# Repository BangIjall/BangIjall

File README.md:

- Hi, I’m Muhammad Rayhan Rizaldi 👋
- I’m interested in robotic
- If u like my projects and want to collaborate with me, u can visit my contacts
- Whatsapp : 082124256955
- Instagram : @rizaldirayhn
- Twitter : @BangIjalll
- Email : mr.rizaldi1629@gmail.com

<!---
BangIjall/BangIjall is a ✨ special ✨ repository because its `README.md` (this file) appears on your GitHub profile.
You can click the Preview link to take a look at your changes.
--->

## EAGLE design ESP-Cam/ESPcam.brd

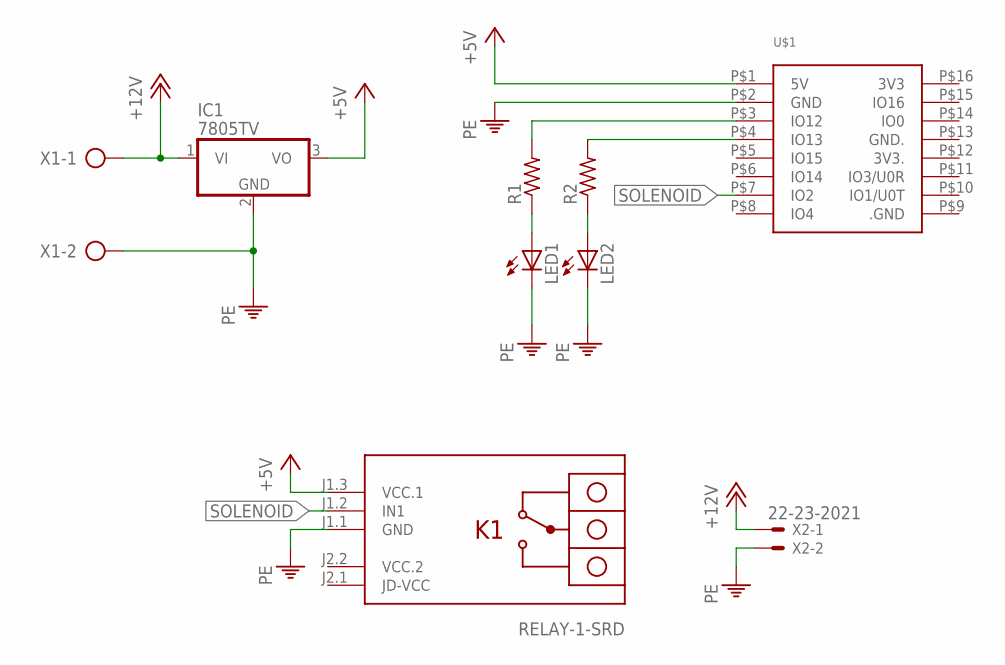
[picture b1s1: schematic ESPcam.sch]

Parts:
IC1: 7805TV; TO220V
LED1, LED2: LED5MM
R1, R2: R-US_0207/15; 0207/15
U$1: ESP32-CAM
U$2: RELAY-1-SRD
X1: AK500/2-H
X2: 22-23-2021

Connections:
+5V: IC1.3 (VO), U$1.P$1 (5V), U$2.J1.3 (VCC.1)
+12V: IC1.1 (VI), X1.1, X2.1
unnamed: LED1.A, R1.1
unnamed: LED2.A, R2.1
unnamed: R1.2, U$1.P$3 (IO12)
unnamed: R2.2, U$1.P$4 (IO13)
PE: IC1.2 (GND), LED1.K (C), LED2.K (C), U$1.P$2 (GND), U$2.J1.1 (GND), X1.2, X2.2
SOLENOID: U$1.P$7 (IO2), U$2.J1.2 (IN1)
VCC.2: U$2.J2.2 (VCC.2)

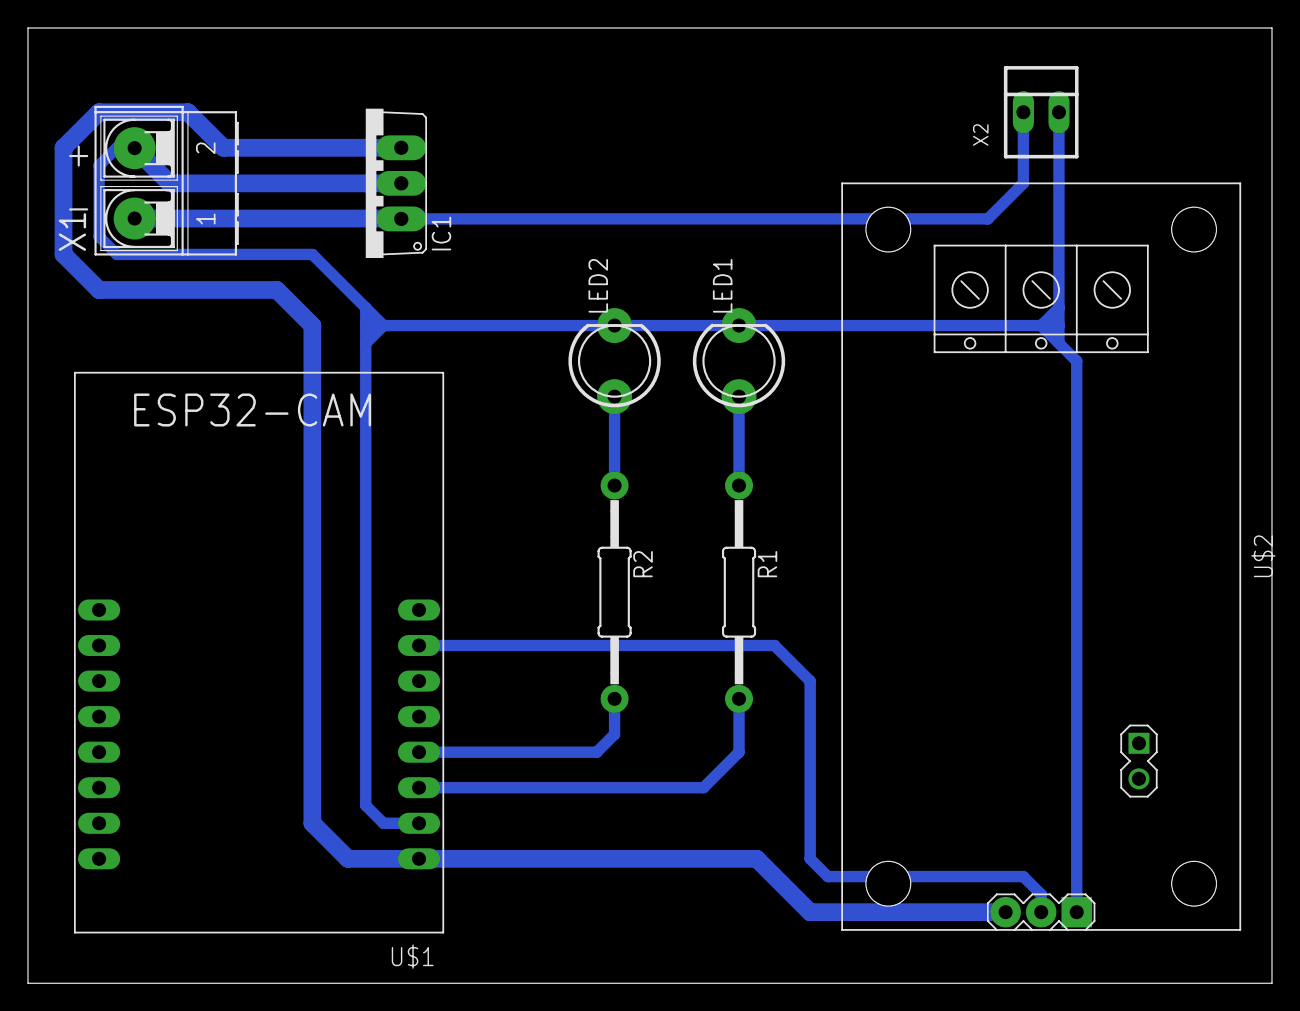
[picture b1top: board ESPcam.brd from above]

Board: 2 copper layers, 88.9 x 68.2 mm, 9 parts (0 on the bottom side), 8 nets.

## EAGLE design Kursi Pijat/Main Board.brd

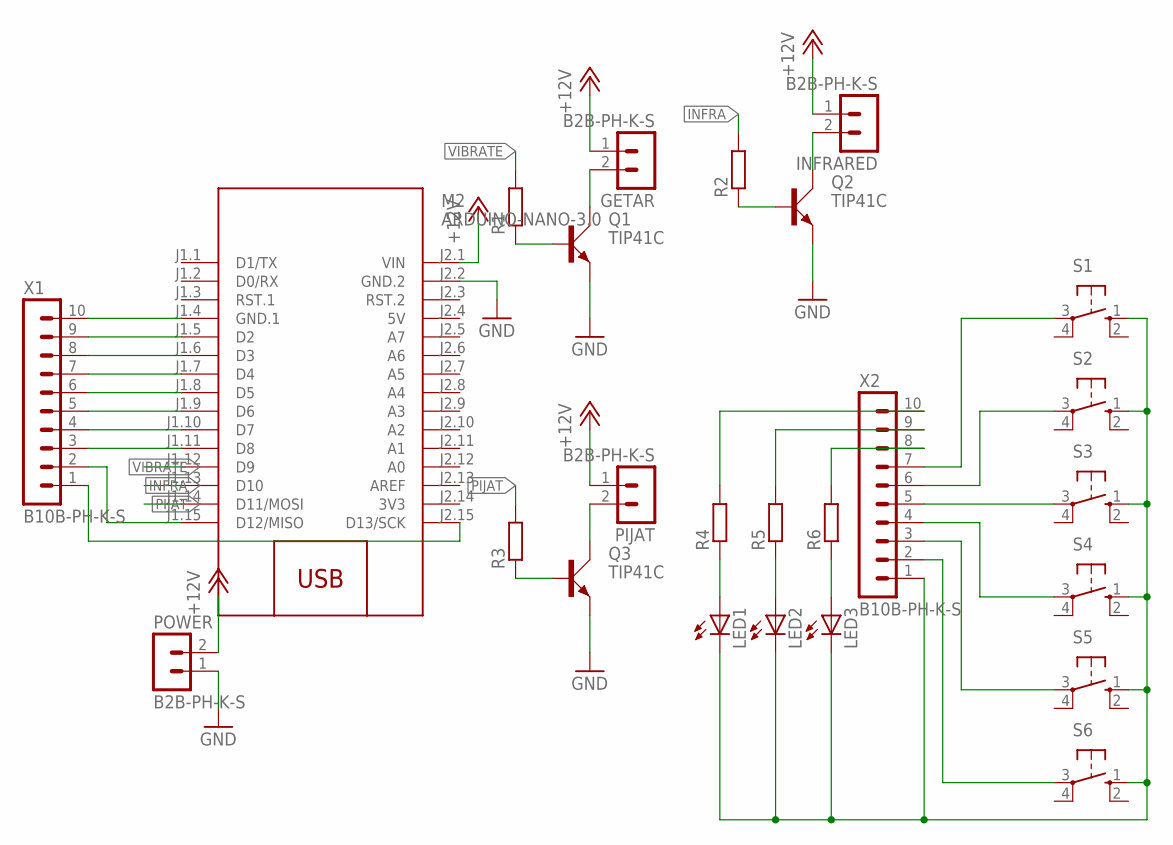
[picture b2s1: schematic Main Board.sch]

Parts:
GETAR: B2B-PH-K-S
INFRARED: B2B-PH-K-S
LED1, LED2, LED3: LED5MM
M2: ARDUINO-NANO-3.0
PIJAT: B2B-PH-K-S
POWER: B2B-PH-K-S
Q1, Q2, Q3: TIP41C; TO220AV
R1, R2, R3, R4, R5, R6: R-EU_0207/12; 0207/12
S1, S2, S3, S4, S5, S6: 40-XX; B3F-40XX
X1, X2: B10B-PH-K-S

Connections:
3V3: M2.J2.14 (3V3)
5V: M2.J2.4 (5V)
+12V: GETAR.1, INFRARED.1, M2.J2.1 (VIN), PIJAT.1, POWER.2
GND: M2.J2.2 (GND.2), POWER.1, Q1.E, Q2.E, Q3.E
INFRA: M2.J1.13 (D10), R2.2
unnamed: INFRARED.2, Q2.C
unnamed: GETAR.2, Q1.C
unnamed: PIJAT.2, Q3.C
unnamed: M2.J1.4 (GND.1), X1.10
unnamed: M2.J1.5 (D2), X1.9
unnamed: M2.J1.6 (D3), X1.8
unnamed: M2.J1.7 (D4), X1.7
unnamed: M2.J1.8 (D5), X1.6
unnamed: M2.J1.9 (D6), X1.5
unnamed: Q2.B, R2.1
unnamed: S1.3, X2.7
unnamed: S2.3, X2.6
unnamed: S5.3, X2.3
unnamed: S4.3, X2.4
unnamed: S3.3, X2.5
unnamed: M2.J1.10 (D7), X1.4
unnamed: Q1.B, R1.1
unnamed: Q3.B, R3.1
unnamed: M2.J1.11 (D8), X1.3
unnamed: M2.J1.15 (D12/MISO), X1.2
unnamed: S6.3, X2.2
unnamed: M2.J2.15 (D13/SCK), X1.1
unnamed: LED1.A, R4.1
unnamed: LED2.A, R5.1
unnamed: LED3.A, R6.1
unnamed: R4.2, X2.10
unnamed: R5.2, X2.9
unnamed: R6.2, X2.8
unnamed: LED1.K (C), LED2.K (C), LED3.K (C), S1.1 (S), S2.1 (S), S3.1 (S), S4.1 (S), S5.1 (S), S6.1 (S), X2.1
PIJAT: M2.J1.14 (D11/MOSI), R3.2
VIBRATE: M2.J1.12 (D9), R1.2

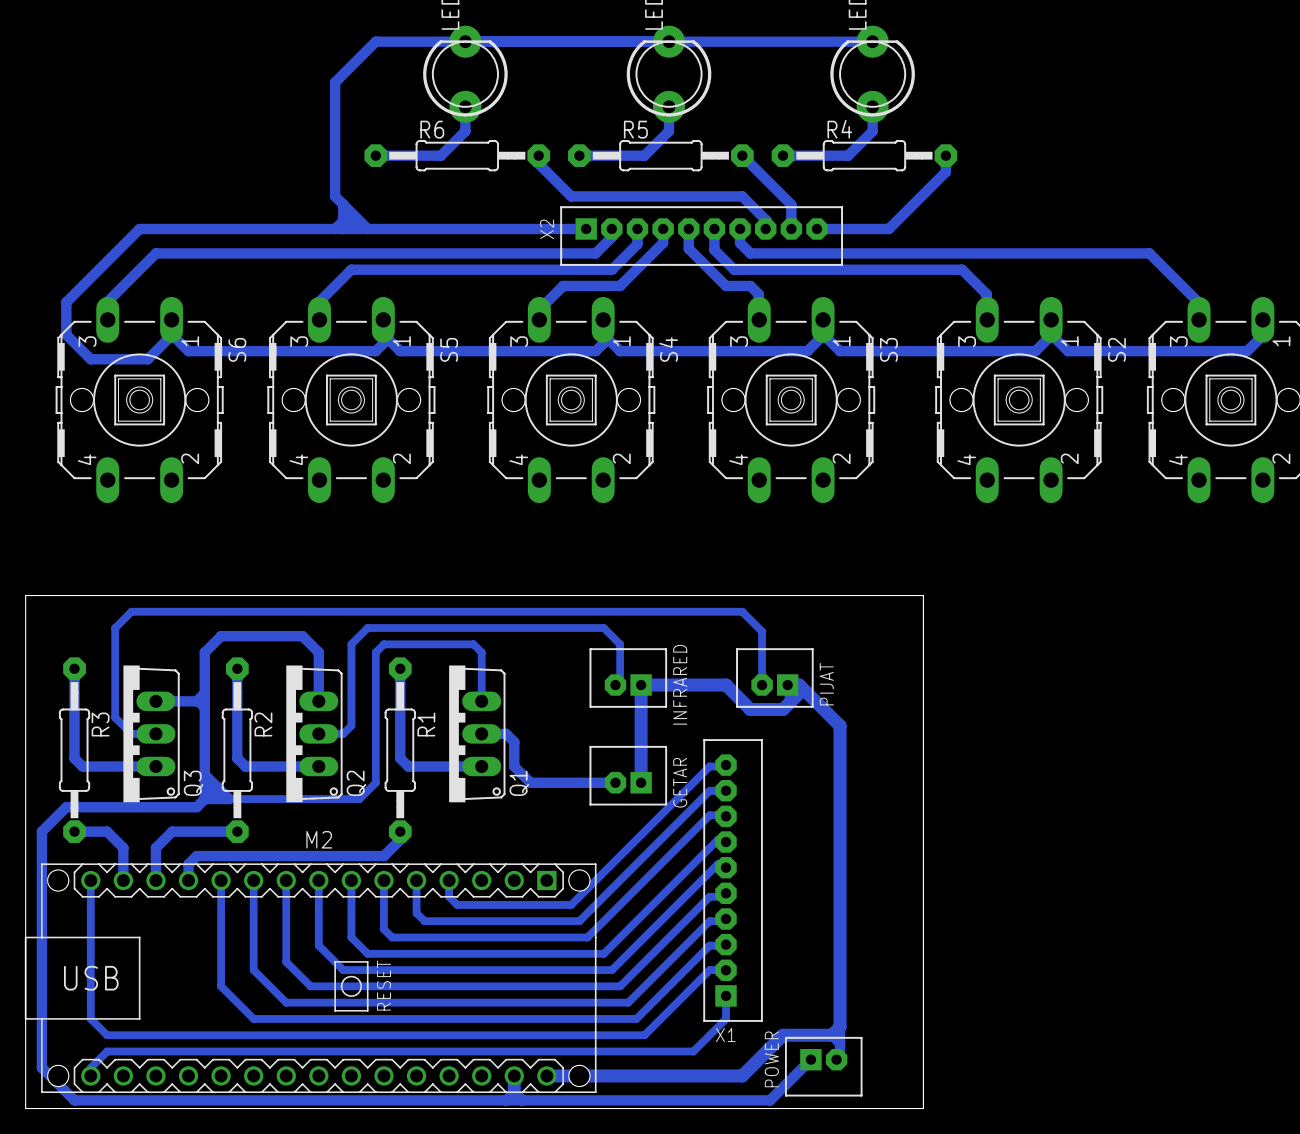
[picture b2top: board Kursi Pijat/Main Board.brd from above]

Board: 2 copper layers, 70.0 x 40.0 mm, 25 parts (0 on the bottom side), 34 nets.

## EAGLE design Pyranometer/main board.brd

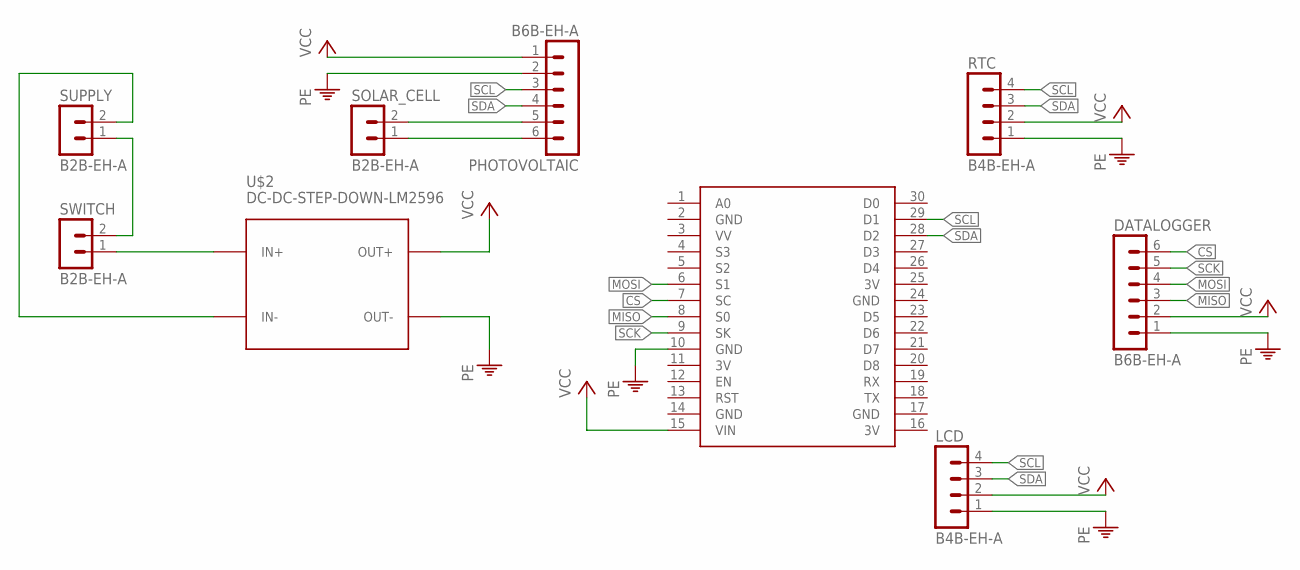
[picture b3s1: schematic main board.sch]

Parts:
DATALOGGER: B6B-EH-A
LCD: B4B-EH-A
PHOTOVOLTAIC: B6B-EH-A
RTC: B4B-EH-A
SOLAR_CELL: B2B-EH-A
SUPPLY: B2B-EH-A
SWITCH: B2B-EH-A
U$1: NODEMCU
U$2: DC-DC-STEP-DOWN-LM2596

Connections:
3V: U$1.11 (3V), U$1.16 (3V), U$1.25 (3V)
CS: DATALOGGER.6, U$1.7 (SC)
GND: U$1.2 (GND), U$1.14 (GND), U$1.17 (GND), U$1.24 (GND)
MISO: DATALOGGER.3, U$1.8 (S0)
MOSI: DATALOGGER.4, U$1.6 (S1)
unnamed: PHOTOVOLTAIC.6, SOLAR_CELL.1
unnamed: SUPPLY.2, U$2.IN-
unnamed: SUPPLY.1, SWITCH.2
unnamed: SWITCH.1, U$2.IN+
unnamed: PHOTOVOLTAIC.5, SOLAR_CELL.2
PE: DATALOGGER.1, LCD.1, PHOTOVOLTAIC.2, RTC.1, U$1.10 (GND), U$2.OUT-
SCK: DATALOGGER.5, U$1.9 (SK)
SCL: LCD.4, PHOTOVOLTAIC.3, RTC.4, U$1.29 (D1)
SDA: LCD.3, PHOTOVOLTAIC.4, RTC.3, U$1.28 (D2)
VCC: DATALOGGER.2, LCD.2, PHOTOVOLTAIC.1, RTC.2, U$1.15 (VIN), U$2.OUT+

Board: 2 copper layers, 9 parts (0 on the bottom side), 15 nets, no tracks yet.

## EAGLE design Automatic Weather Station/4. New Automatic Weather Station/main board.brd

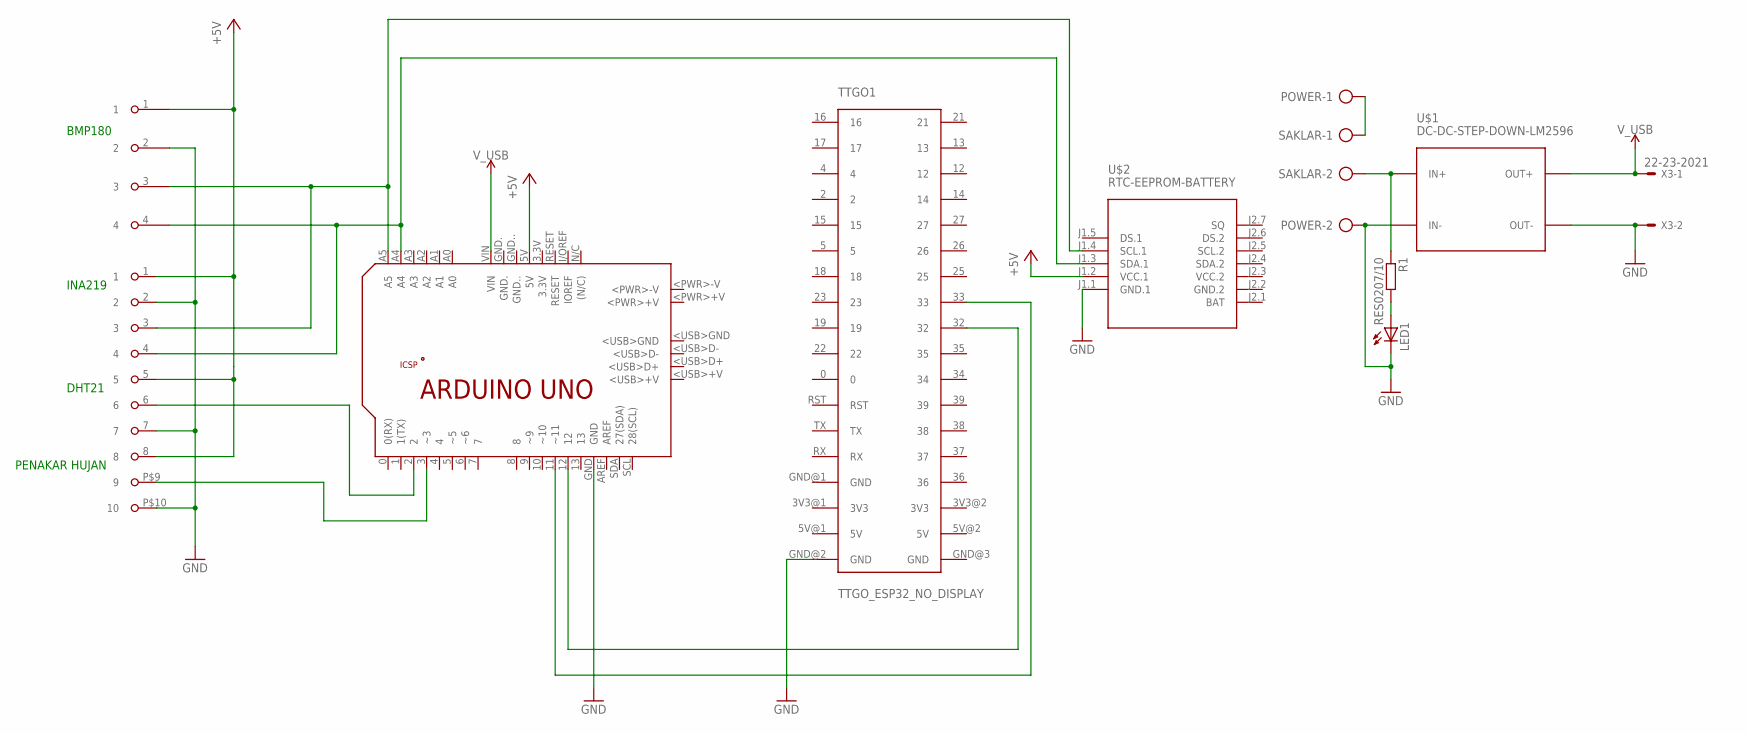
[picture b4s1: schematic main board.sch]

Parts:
LED1: LED5MM
PCB1: ARDUINO_UNO
POWER: AK500/2-H
R1: RES0207/10; 0207/10
SAKLAR: AK500/2-H
TTGO1: TTGO_ESP32_NO_DISPLAY
U$1: DC-DC-STEP-DOWN-LM2596
U$2: RTC-EEPROM-BATTERY
U$3: CON-10TA
U$4: CON-4NEW2; CON-4NEW
X3: 22-23-2021

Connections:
+5V: PCB1.5V, U$2.J1.2 (VCC.1), U$3.1, U$3.5, U$3.8, U$4.1
GND.2: U$2.J2.2 (GND.2)
unnamed: R1.1, SAKLAR.2, U$1.IN+
unnamed: LED1.A, R1.2
unnamed: POWER.1, SAKLAR.1
unnamed: PCB1.A5, U$2.J1.4 (SCL.1), U$3.3, U$4.3
unnamed: PCB1.A4, U$2.J1.3 (SDA.1), U$3.4, U$4.4
unnamed: PCB1.2, U$3.6
unnamed: PCB1.3 (~3), U$3.P$9 (9)
unnamed: PCB1.11 (~11), TTGO1.33
unnamed: PCB1.12, TTGO1.32
unnamed: LED1.K (C), PCB1.GND, POWER.2, TTGO1.GND@2 (GND), U$1.IN-, U$1.OUT-, U$2.J1.1 (GND.1), U$3.2, U$3.7, U$3.P$10 (10), U$4.2, X3.2
VCC.2: U$2.J2.3 (VCC.2)
V_USB: PCB1.VIN, U$1.OUT+, X3.1

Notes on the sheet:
BMP180
INA219
DHT21
PENAKAR HUJAN

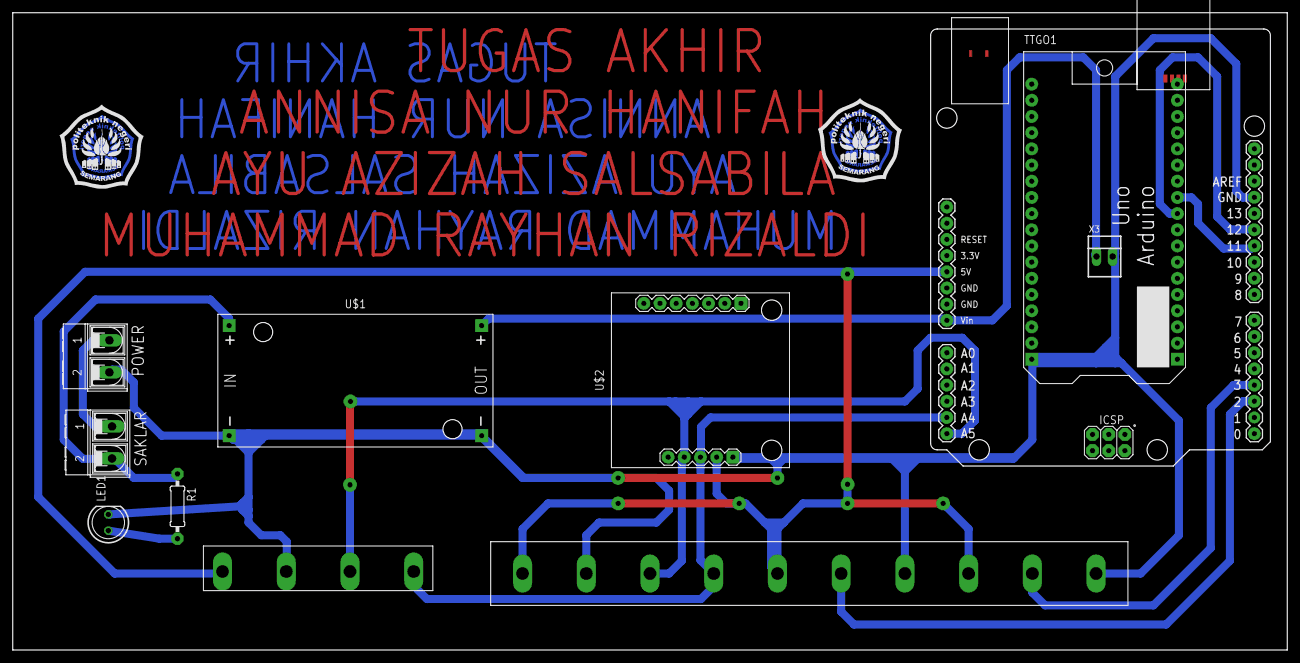
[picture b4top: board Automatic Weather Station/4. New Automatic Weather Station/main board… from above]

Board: 2 copper layers, 200.0 x 100.0 mm, 15 parts (0 on the bottom side), 12 nets.

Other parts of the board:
U$5, U$6: POLINES_10X10_BOT
U$7, U$8: POLINES_13.5X13.5

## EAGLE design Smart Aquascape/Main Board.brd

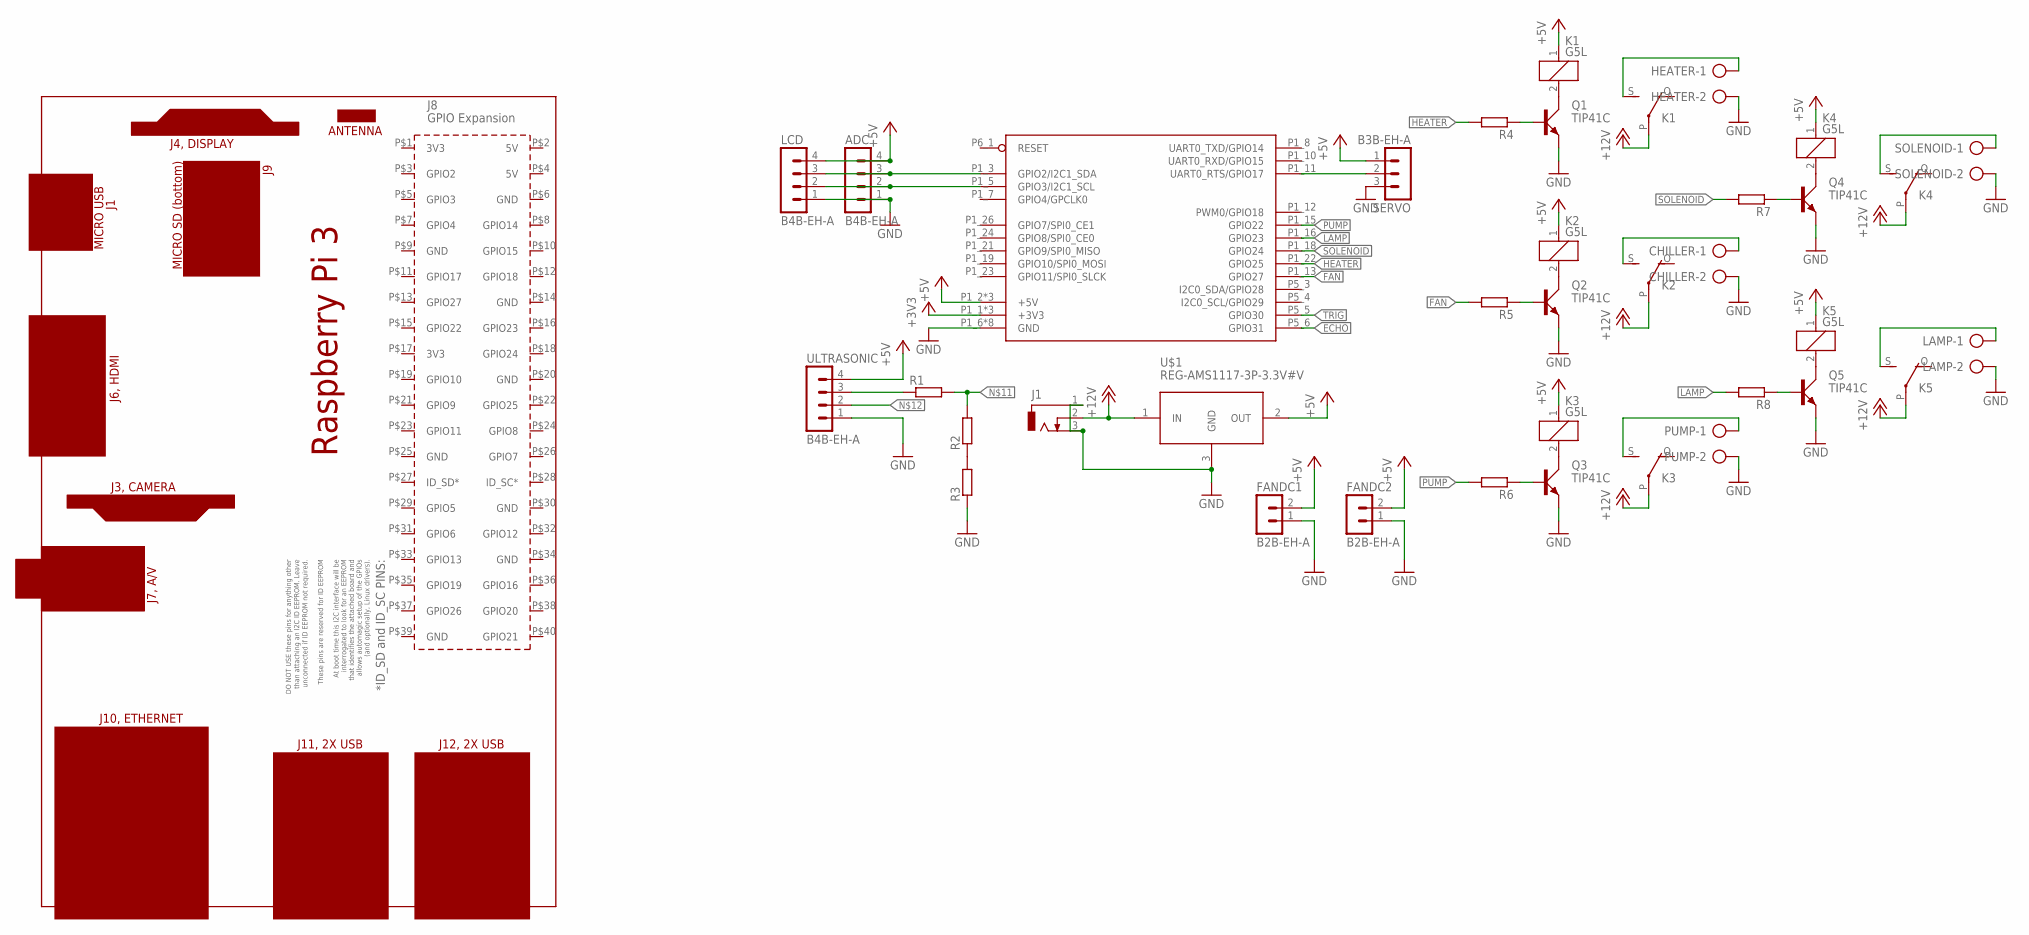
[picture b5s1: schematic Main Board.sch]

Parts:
ADC: B4B-EH-A
CHILLER: AK500/2-H
FANDC1, FANDC2: B2B-EH-A
HEATER: AK500/2-H
J1: DCJ0303
K1, K2, K3, K4, K5: G5L; G5LE
LAMP: AK500/2-H
LCD: B4B-EH-A
PCB1: RPI3
PUMP: AK500/2-H
Q1, Q2, Q3, Q4, Q5: TIP41C; TO220AV
R1, R2, R3, R4, R5, R6, R7, R8: R-EU_0207/15; 0207/15
SERVO: B3B-EH-A
SOLENOID: AK500/2-H
U$1: REG-AMS1117-3P-3.3V#V; REG-AMS1117-3P#V
U$3: RPI-B-V2NO_SHIELD; RPI-B-V2
ULTRASONIC: B4B-EH-A

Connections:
+3V3: U$3.P1_1 (+3V3), U$3.P1_17 (+3V3), U$3.P5_2 (+3V3)
+5V: ADC.4, FANDC1.2, FANDC2.2, K1.1, K2.1, K3.1, K4.1, K5.1, LCD.4, SERVO.1, U$1.2 (OUT), U$3.P1_2 (+5V), U$3.P1_4 (+5V), U$3.P5_1 (+5V), ULTRASONIC.4
+12V: J1.2, K1.P, K2.P, K3.P, K4.P, K5.P, U$1.1 (IN)
ECHO: U$3.P5_6 (GPIO31)
FAN: R5.2, U$3.P1_13 (GPIO27)
GND: ADC.1, CHILLER.2, FANDC1.1, FANDC2.1, HEATER.2, J1.1, J1.3, LAMP.2, LCD.1, PUMP.2, Q1.E, Q2.E, Q3.E, Q4.E, Q5.E, R3.1, SERVO.3, SOLENOID.2, U$1.3 (GND), U$3.P1_6 (GND), U$3.P1_9 (GND), U$3.P1_14 (GND), U$3.P1_20 (GND), U$3.P1_25 (GND), U$3.P5_7 (GND), U$3.P5_8 (GND), U$3.P6_2 (GND), ULTRASONIC.1
HEATER: R4.2, U$3.P1_22 (GPIO25)
I2C0_SCL/GPIO29: U$3.P5_4 (I2C0_SCL/GPIO29)
I2C0_SDA/GPIO28: U$3.P5_3 (I2C0_SDA/GPIO28)
LAMP: R8.2, U$3.P1_16 (GPIO23)
unnamed: ADC.3, LCD.3, U$3.P1_3 (GPIO2/I2C1_SDA)
unnamed: ADC.2, LCD.2, U$3.P1_5 (GPIO3/I2C1_SCL)
unnamed: K3.S, PUMP.1
unnamed: K3.2, Q3.C
unnamed: Q3.B, R6.1
unnamed: CHILLER.1, K2.S
unnamed: HEATER.1, K1.S
unnamed: SERVO.2, U$3.P1_11 (UART0_RTS/GPIO17)
unnamed: R2.1, R3.2
unnamed: R1.1, ULTRASONIC.3
unnamed: R1.2, R2.2
unnamed: K1.2, Q1.C
unnamed: Q1.B, R4.1
unnamed: K2.2, Q2.C
unnamed: Q2.B, R5.1
unnamed: K4.S, SOLENOID.1
unnamed: K4.2, Q4.C
unnamed: Q4.B, R7.1
unnamed: K5.S, LAMP.1
unnamed: K5.2, Q5.C
unnamed: Q5.B, R8.1
PUMP: R6.2, U$3.P1_15 (GPIO22)
RESET: U$3.P6_1 (RESET)
SOLENOID: R7.2, U$3.P1_18 (GPIO24)
TRIG: U$3.P5_5 (GPIO30)

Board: 2 copper layers, 33 parts (0 on the bottom side), 30 nets, no tracks yet.

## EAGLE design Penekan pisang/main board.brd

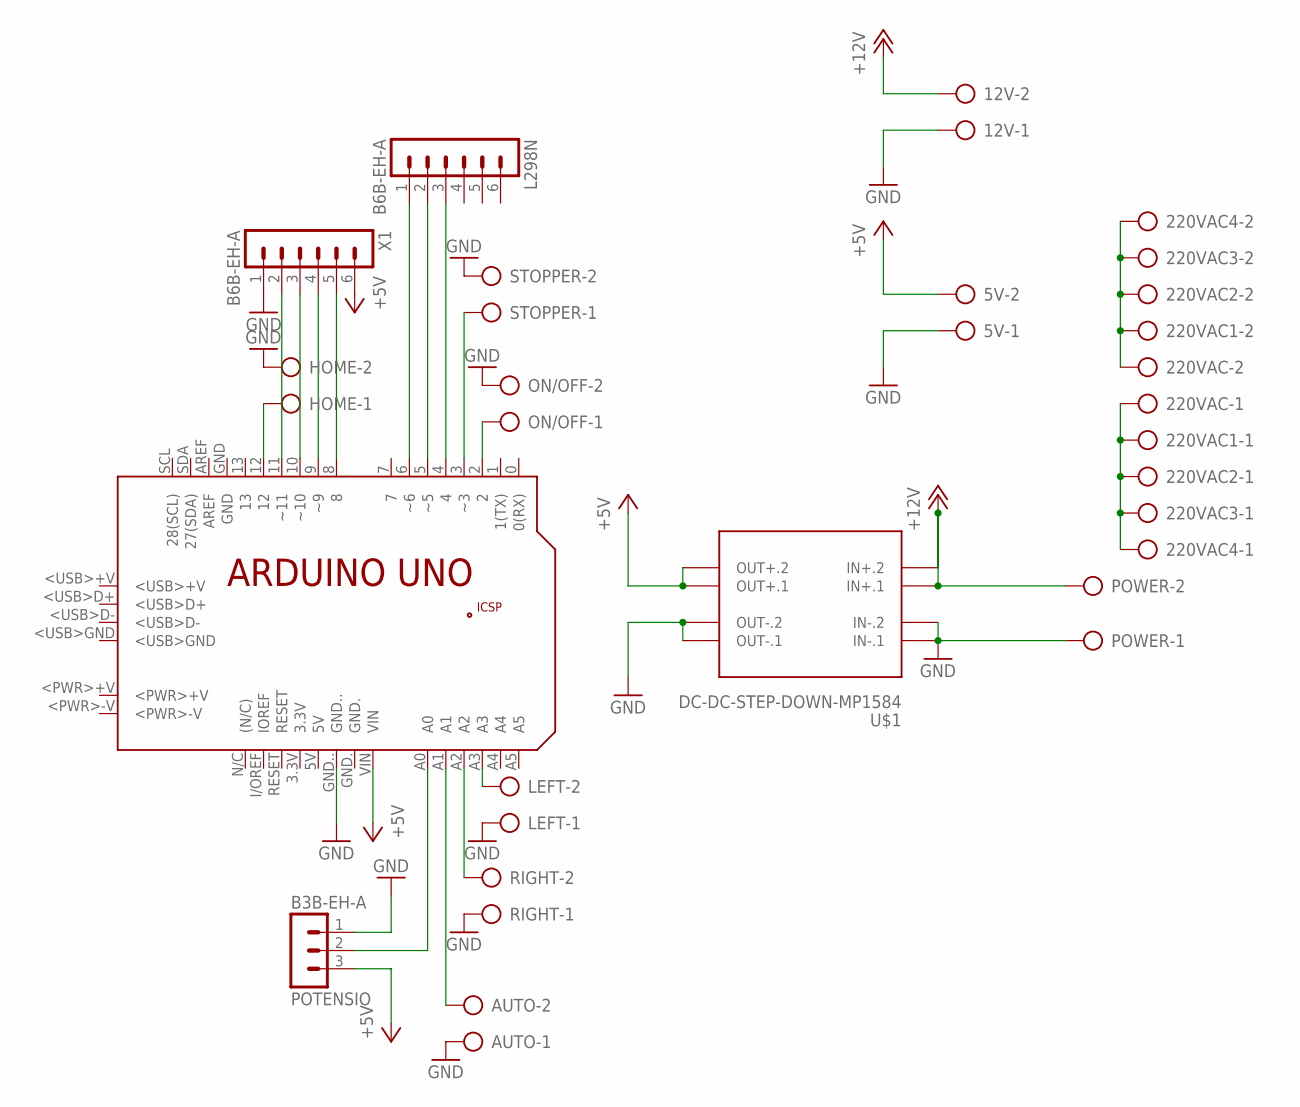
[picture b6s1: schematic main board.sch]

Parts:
5V, 12V, 220VAC, 220VAC1, 220VAC2, 220VAC3, 220VAC4: AK500/2-H
AUTO: AK500/2-H
HOME: AK500/2-H
L298N: B6B-EH-A
LEFT: AK500/2-H
ON/OFF: AK500/2-H
PCB1: ARDUINO_UNO
POTENSIO: B3B-EH-A
POWER: AK500/2-H
RIGHT: AK500/2-H
STOPPER: AK500/2-H
U$1: DC-DC-STEP-DOWN-MP1584
X1: B6B-EH-A

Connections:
+5V: 5V.2, PCB1.VIN, POTENSIO.3, U$1.OUT+.1, U$1.OUT+.2, X1.6
+12V: 12V.2, POWER.2, U$1.IN+.1, U$1.IN+.2
GND: 5V.1, 12V.1, AUTO.1, HOME.2, LEFT.1, ON/OFF.2, PCB1.GND.., POTENSIO.1, POWER.1, RIGHT.1, STOPPER.2, U$1.IN-.1, U$1.IN-.2, U$1.OUT-.1, U$1.OUT-.2, X1.1
unnamed: L298N.2, PCB1.5 (~5)
unnamed: L298N.3, PCB1.4
unnamed: L298N.1, PCB1.6 (~6)
unnamed: AUTO.2, PCB1.A1
unnamed: PCB1.11 (~11), X1.2
unnamed: PCB1.A0, POTENSIO.2
unnamed: PCB1.10 (~10), X1.3
unnamed: PCB1.9 (~9), X1.4
unnamed: PCB1.8, X1.5
unnamed: PCB1.A2, RIGHT.2
unnamed: LEFT.2, PCB1.A3
unnamed: PCB1.3 (~3), STOPPER.1
unnamed: HOME.1, PCB1.12
unnamed: ON/OFF.1, PCB1.2
unnamed: 220VAC.1, 220VAC1.1, 220VAC2.1, 220VAC3.1, 220VAC4.1
unnamed: 220VAC.2, 220VAC1.2, 220VAC2.2, 220VAC3.2, 220VAC4.2

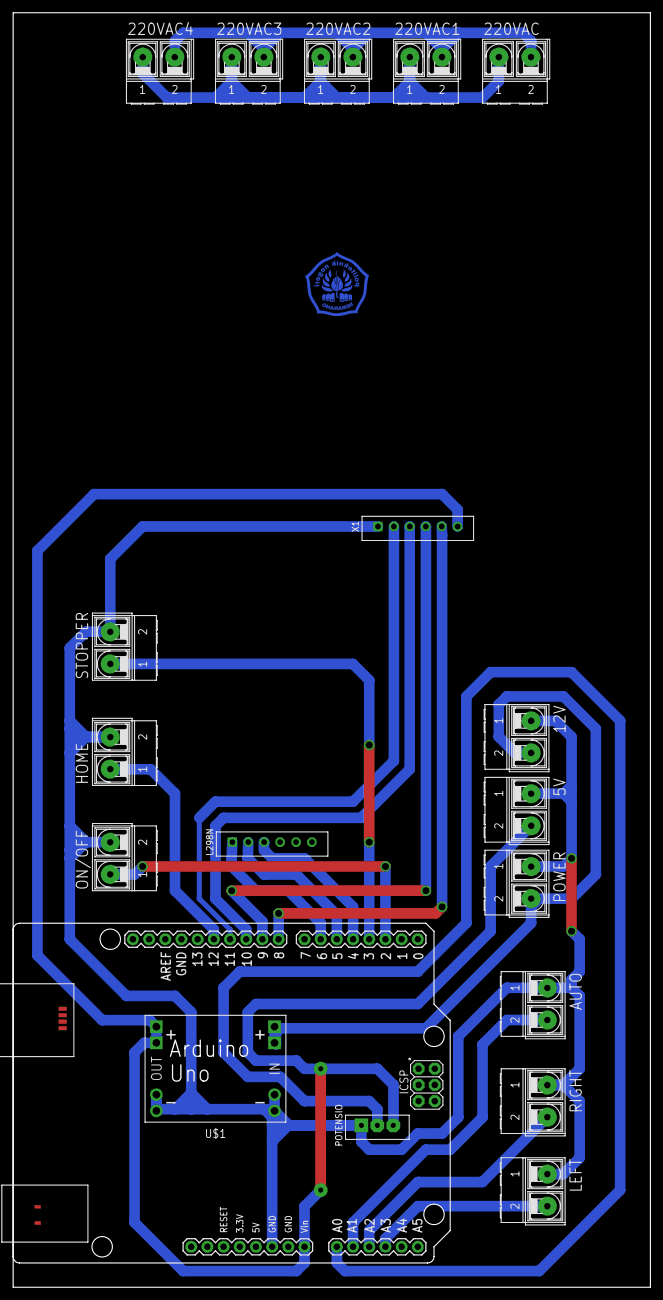
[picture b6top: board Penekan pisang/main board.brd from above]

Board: 2 copper layers, 100.0 x 200.0 mm, 20 parts (0 on the bottom side), 19 nets.

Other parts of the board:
U$2: POLINES_10X10_BOT

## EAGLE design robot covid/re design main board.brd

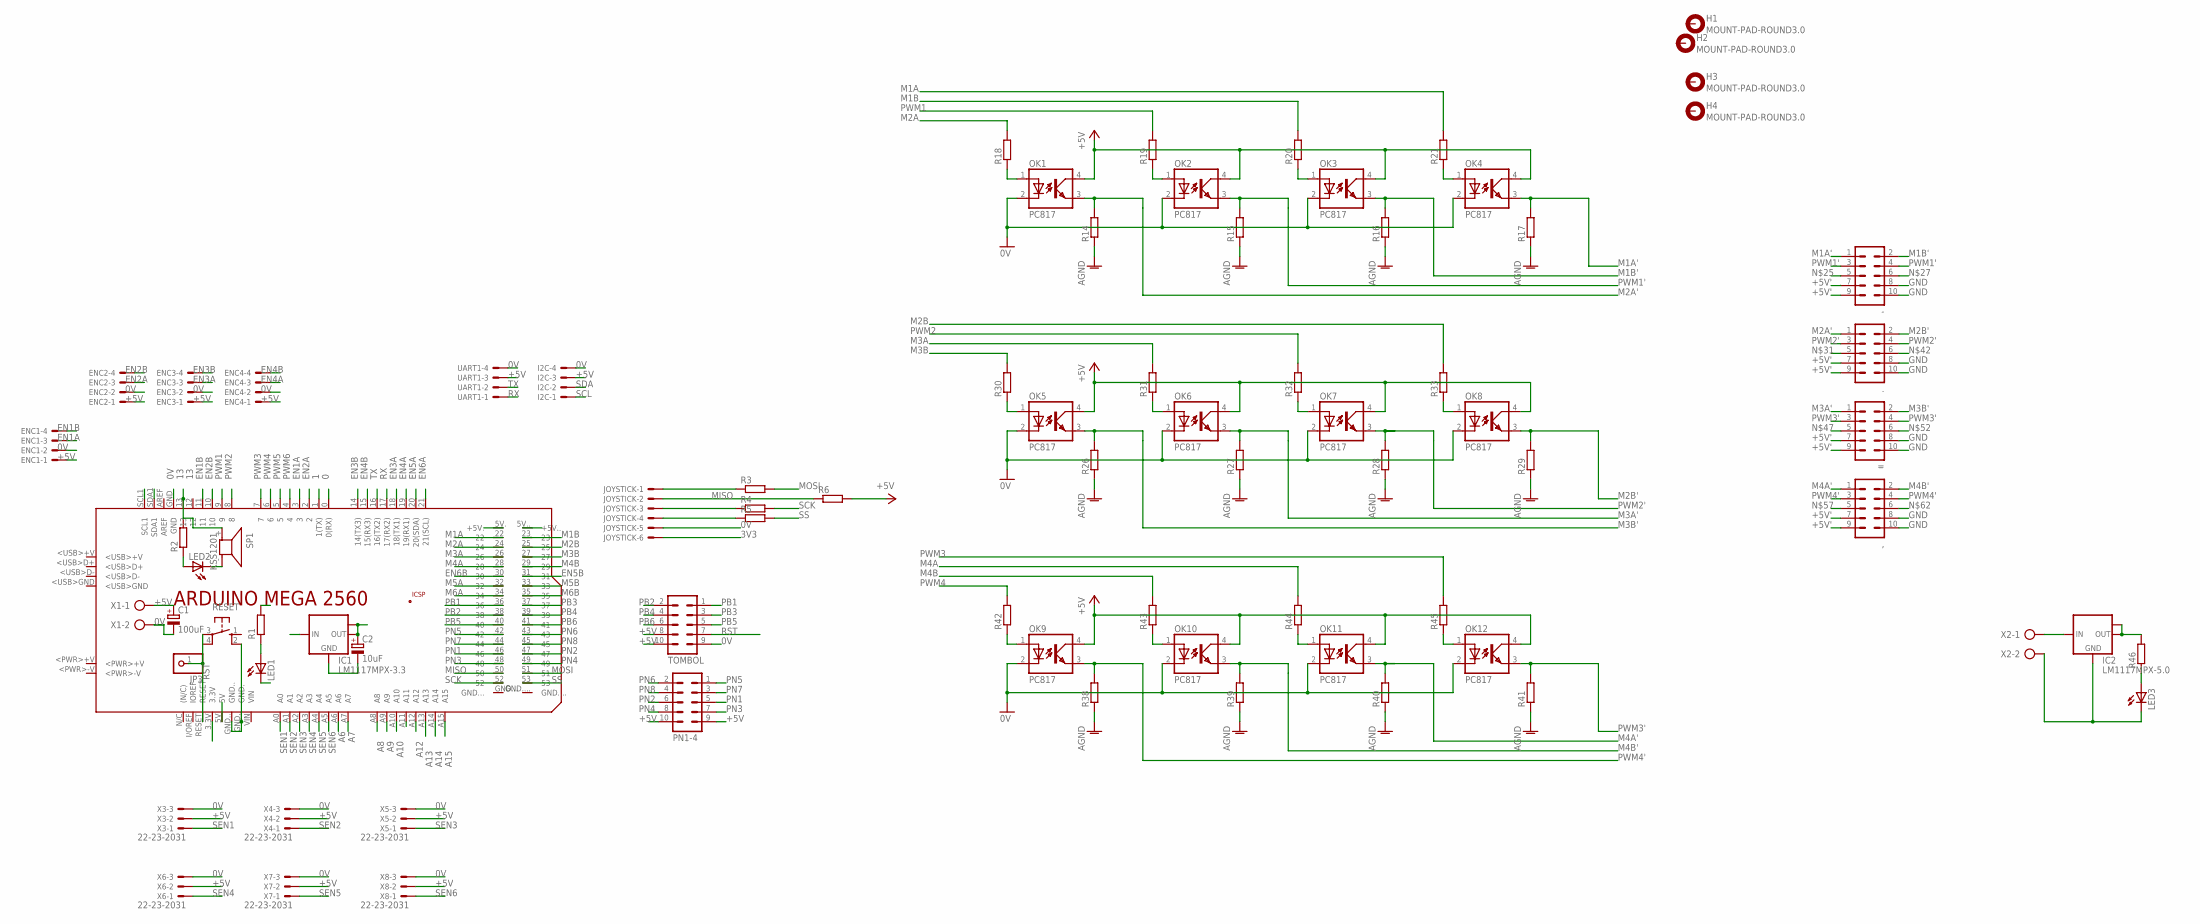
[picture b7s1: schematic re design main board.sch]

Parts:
,: ML10
-: ML10
.: ML10
=: ML10
C1: 100uF; E2,5-5
C2: 10uF; E2,5-5
ENC1, ENC2, ENC3, ENC4: 22-23-2041
H1, H2, H3, H4: MOUNT-PAD-ROUND3.0; 3,0-PAD
I2C: 22-23-2041
IC1: LM1117MPX-3.3; SOT223
IC2: LM1117MPX-5.0; SOT223
JOYSTICK: 22-23-2061
JP3: PINHD-1X1; 1X01
LED1, LED2, LED3: LED3MM
OK1, OK2, OK3, OK4, OK5, OK6, OK7, OK8, OK9, OK10, OK11, OK12: PC817; DIL04
PCB1: ARDUINO_MEGA2560
PN1-4: ML10
R1, R2, R14, R15, R16, R17, R18, R19, R20, R21, R26, R27, R28, R29, R30, R31, R32, R33, R38, R39, R40, R41, R42, R43, R44, R45: R-EU_M0805; M0805
R3, R4, R5, R6: R-EU_R0805; R0805
R46: R-EU_0207/10; 0207/10
RESET: 40-XX; B3F-40XX
SP1: KSS1201
TOMBOL: ML10
UART1: 22-23-2041
X1: AK500/2
X2: AK300/2
X3, X4, X5, X6, X7, X8: 22-23-2031

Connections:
0: PCB1.0 (0(RX))
0V: C1.-, ENC1.2, ENC2.2, ENC3.2, ENC4.2, I2C.4, JOYSTICK.5, LED1.K (C), LED2.K (C), OK1.2 (C), OK2.2 (C), OK3.2 (C), OK4.2 (C), OK5.2 (C), OK6.2 (C), OK7.2 (C), OK8.2 (C), OK9.2 (C), OK10.2 (C), OK11.2 (C), OK12.2 (C), PCB1.GND, PCB1.GND., PCB1.GND.., RESET.2 (S1), SP1.- (2), TOMBOL.9, UART1.4, X1.2, X3.3, X4.3, X5.3, X6.3, X7.3, X8.3
1: PCB1.1 (1(TX))
3V3: C2.+, IC1.2 (OUT), IC1.TAB (OUT1), JOYSTICK.6, PCB1.3.3V
13: PCB1.13, R2.2, SP1.+ (1)
+5V: C1.+, ENC1.1, ENC2.1, ENC3.1, ENC4.1, I2C.3, IC1.3 (IN), PCB1.5V, PCB1.5V. (+5V.), PCB1.5V.. (+5V..), PN1-4.9, PN1-4.10, R1.2, R6.2, TOMBOL.8, TOMBOL.10, UART1.3, X1.1, X3.2, X4.2, X5.2, X6.2, X7.2, X8.2
+5V': ,.7, ,.9, -.7, -.9, ..7, ..9, =.7, =.9, IC2.2 (OUT), IC2.TAB (OUT1), OK1.4 (COL), OK2.4 (COL), OK3.4 (COL), OK4.4 (COL), OK5.4 (COL), OK6.4 (COL), OK7.4 (COL), OK8.4 (COL), OK9.4 (COL), OK10.4 (COL), OK11.4 (COL), OK12.4 (COL), R46.2
A6: PCB1.A6
A7: PCB1.A7
A8: PCB1.A8
A9: PCB1.A9
A10: PCB1.A10
A11: PCB1.A11
A12: PCB1.A12
A13: PCB1.A13
A14: PCB1.A14
A15: PCB1.A15
EN1A: ENC1.3, PCB1.3
EN1B: ENC1.4, PCB1.11
EN2A: ENC2.3, PCB1.2
EN2B: ENC2.4, PCB1.10
EN3A: ENC3.3, PCB1.18 (18(TX1))
EN3B: ENC3.4, PCB1.14 (14(TX3))
EN4A: ENC4.3, PCB1.19 (19(RX1))
EN4B: ENC4.4, PCB1.15 (15(RX3))
EN5A: PCB1.20 (20(SDA))
EN5B: PCB1.31
EN6A: PCB1.21 (21(SCL))
EN6B: PCB1.30
GND: ,.8, ,.10, -.8, -.10, ..8, ..10, =.8, =.10, IC2.1 (GND), LED3.K (C), R14.1, R15.1, R16.1, R17.1, R26.1, R27.1, R28.1, R29.1, R38.1, R39.1, R40.1, R41.1, X2.2
M1A: PCB1.22, R21.2
M1A': -.1, OK4.3 (EMIT), R17.2
M1B: PCB1.23, R20.2
M1B': -.2, OK3.3 (EMIT), R16.2
M2A: PCB1.24, R18.2
M2A': ..1, OK1.3 (EMIT), R14.2
M2B: PCB1.25, R33.2
M2B': ..2, OK8.3 (EMIT), R29.2
M3A: PCB1.26, R31.2
M3A': =.1, OK6.3 (EMIT), R27.2
M3B: PCB1.27, R30.2
M3B': =.2, OK5.3 (EMIT), R26.2
M4A: PCB1.28, R44.2
M4A': ,.1, OK11.3 (EMIT), R40.2
M4B: PCB1.29, R43.2
M4B': ,.2, OK10.3 (EMIT), R39.2
M5A: PCB1.32
M5B: PCB1.33
M6A: PCB1.34
M6B: PCB1.35
MISO: JOYSTICK.2, PCB1.50, R6.1
MOSI: PCB1.51, R3.2
unnamed: LED1.A, R1.1
unnamed: LED2.A, R2.1
unnamed: C2.-, IC1.1 (GND)
unnamed: OK1.1 (A), R18.1
unnamed: OK2.1 (A), R19.1
unnamed: OK3.1 (A), R20.1
unnamed: OK4.1 (A), R21.1
unnamed: OK5.1 (A), R30.1
unnamed: OK6.1 (A), R31.1
unnamed: OK7.1 (A), R32.1
unnamed: OK8.1 (A), R33.1
unnamed: JOYSTICK.1, R3.1
unnamed: JOYSTICK.3, R4.1
unnamed: JOYSTICK.4, R5.1
unnamed: LED3.A, R46.1
unnamed: IC2.3 (IN), X2.1
unnamed: OK9.1 (A), R42.1
unnamed: OK10.1 (A), R43.1
unnamed: OK11.1 (A), R44.1
unnamed: OK12.1 (A), R45.1
PB1: PCB1.36, TOMBOL.1
PB2: PCB1.38, TOMBOL.2
PB3: PCB1.37, TOMBOL.3
PB4: PCB1.39, TOMBOL.4
PB5: PCB1.40, TOMBOL.5
PB6: PCB1.41, TOMBOL.6
PN1: PCB1.46, PN1-4.5
PN2: PCB1.47, PN1-4.6
PN3: PCB1.48, PN1-4.7
PN4: PCB1.49, PN1-4.8
PN5: PCB1.42, PN1-4.1
PN6: PCB1.43, PN1-4.2
PN7: PCB1.44, PN1-4.3
PN8: PCB1.45, PN1-4.4
PWM1: PCB1.9, R19.2
PWM1': -.3, -.4, OK2.3 (EMIT), R15.2
PWM2: PCB1.8, R32.2
PWM2': ..3, ..4, OK7.3 (EMIT), R28.2
PWM3: PCB1.7, R45.2
PWM3': =.3, =.4, OK12.3 (EMIT), R41.2
PWM4: PCB1.6, R42.2
PWM4': ,.3, ,.4, OK9.3 (EMIT), R38.2
PWM5: PCB1.5
PWM6: PCB1.4
RST: JP3.1, PCB1.RESET, RESET.3, TOMBOL.7
RX: PCB1.17 (17(RX2)), UART1.1
SCK: PCB1.52, R4.2
SCL: I2C.1, PCB1.SCL1
SDA: I2C.2, PCB1.SDA1
SEN1: PCB1.A0, X3.1
SEN2: PCB1.A1, X4.1
SEN3: PCB1.A2, X5.1
SEN4: PCB1.A3, X6.1
SEN5: PCB1.A4, X7.1
SEN6: PCB1.A5, X8.1
SS: PCB1.53, R5.2
TX: PCB1.16 (16(TX2)), UART1.2

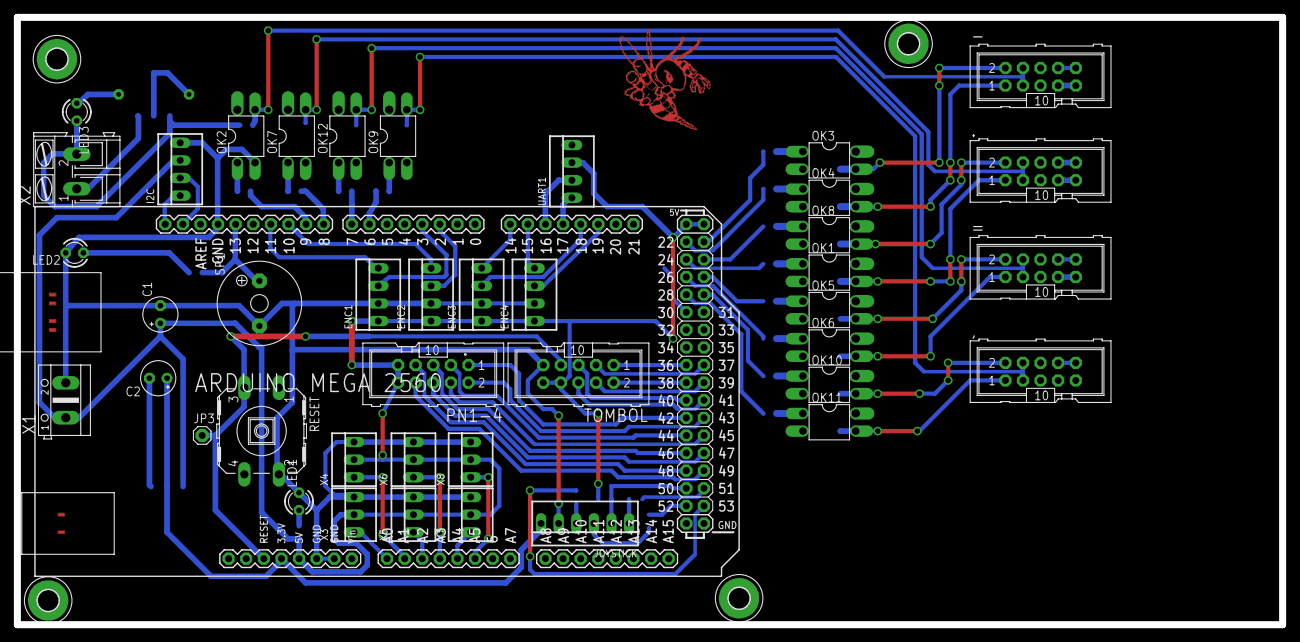
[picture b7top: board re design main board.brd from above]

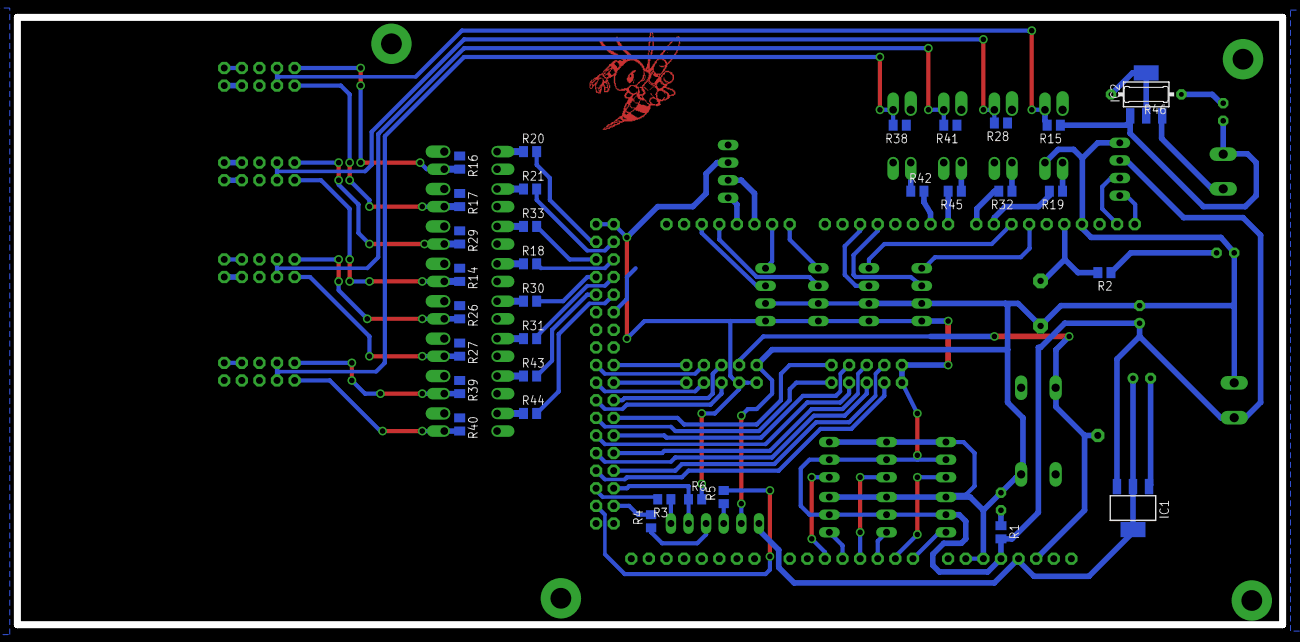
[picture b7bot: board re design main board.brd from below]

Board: 2 copper layers, 182.6 x 87.6 mm, 79 parts (33 on the bottom side), 87 nets.

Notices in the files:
parts and their libraries:
diy-modules: Released under the Creative Commons Attribution 4.0 International License: http://creativecommons.org/licenses/by/4.0
SparkFun-PowerSymbols: Licensing: Creative Commons ShareAlike 4.0 International - https://creativecommons.org/licenses/by-sa/4.0
